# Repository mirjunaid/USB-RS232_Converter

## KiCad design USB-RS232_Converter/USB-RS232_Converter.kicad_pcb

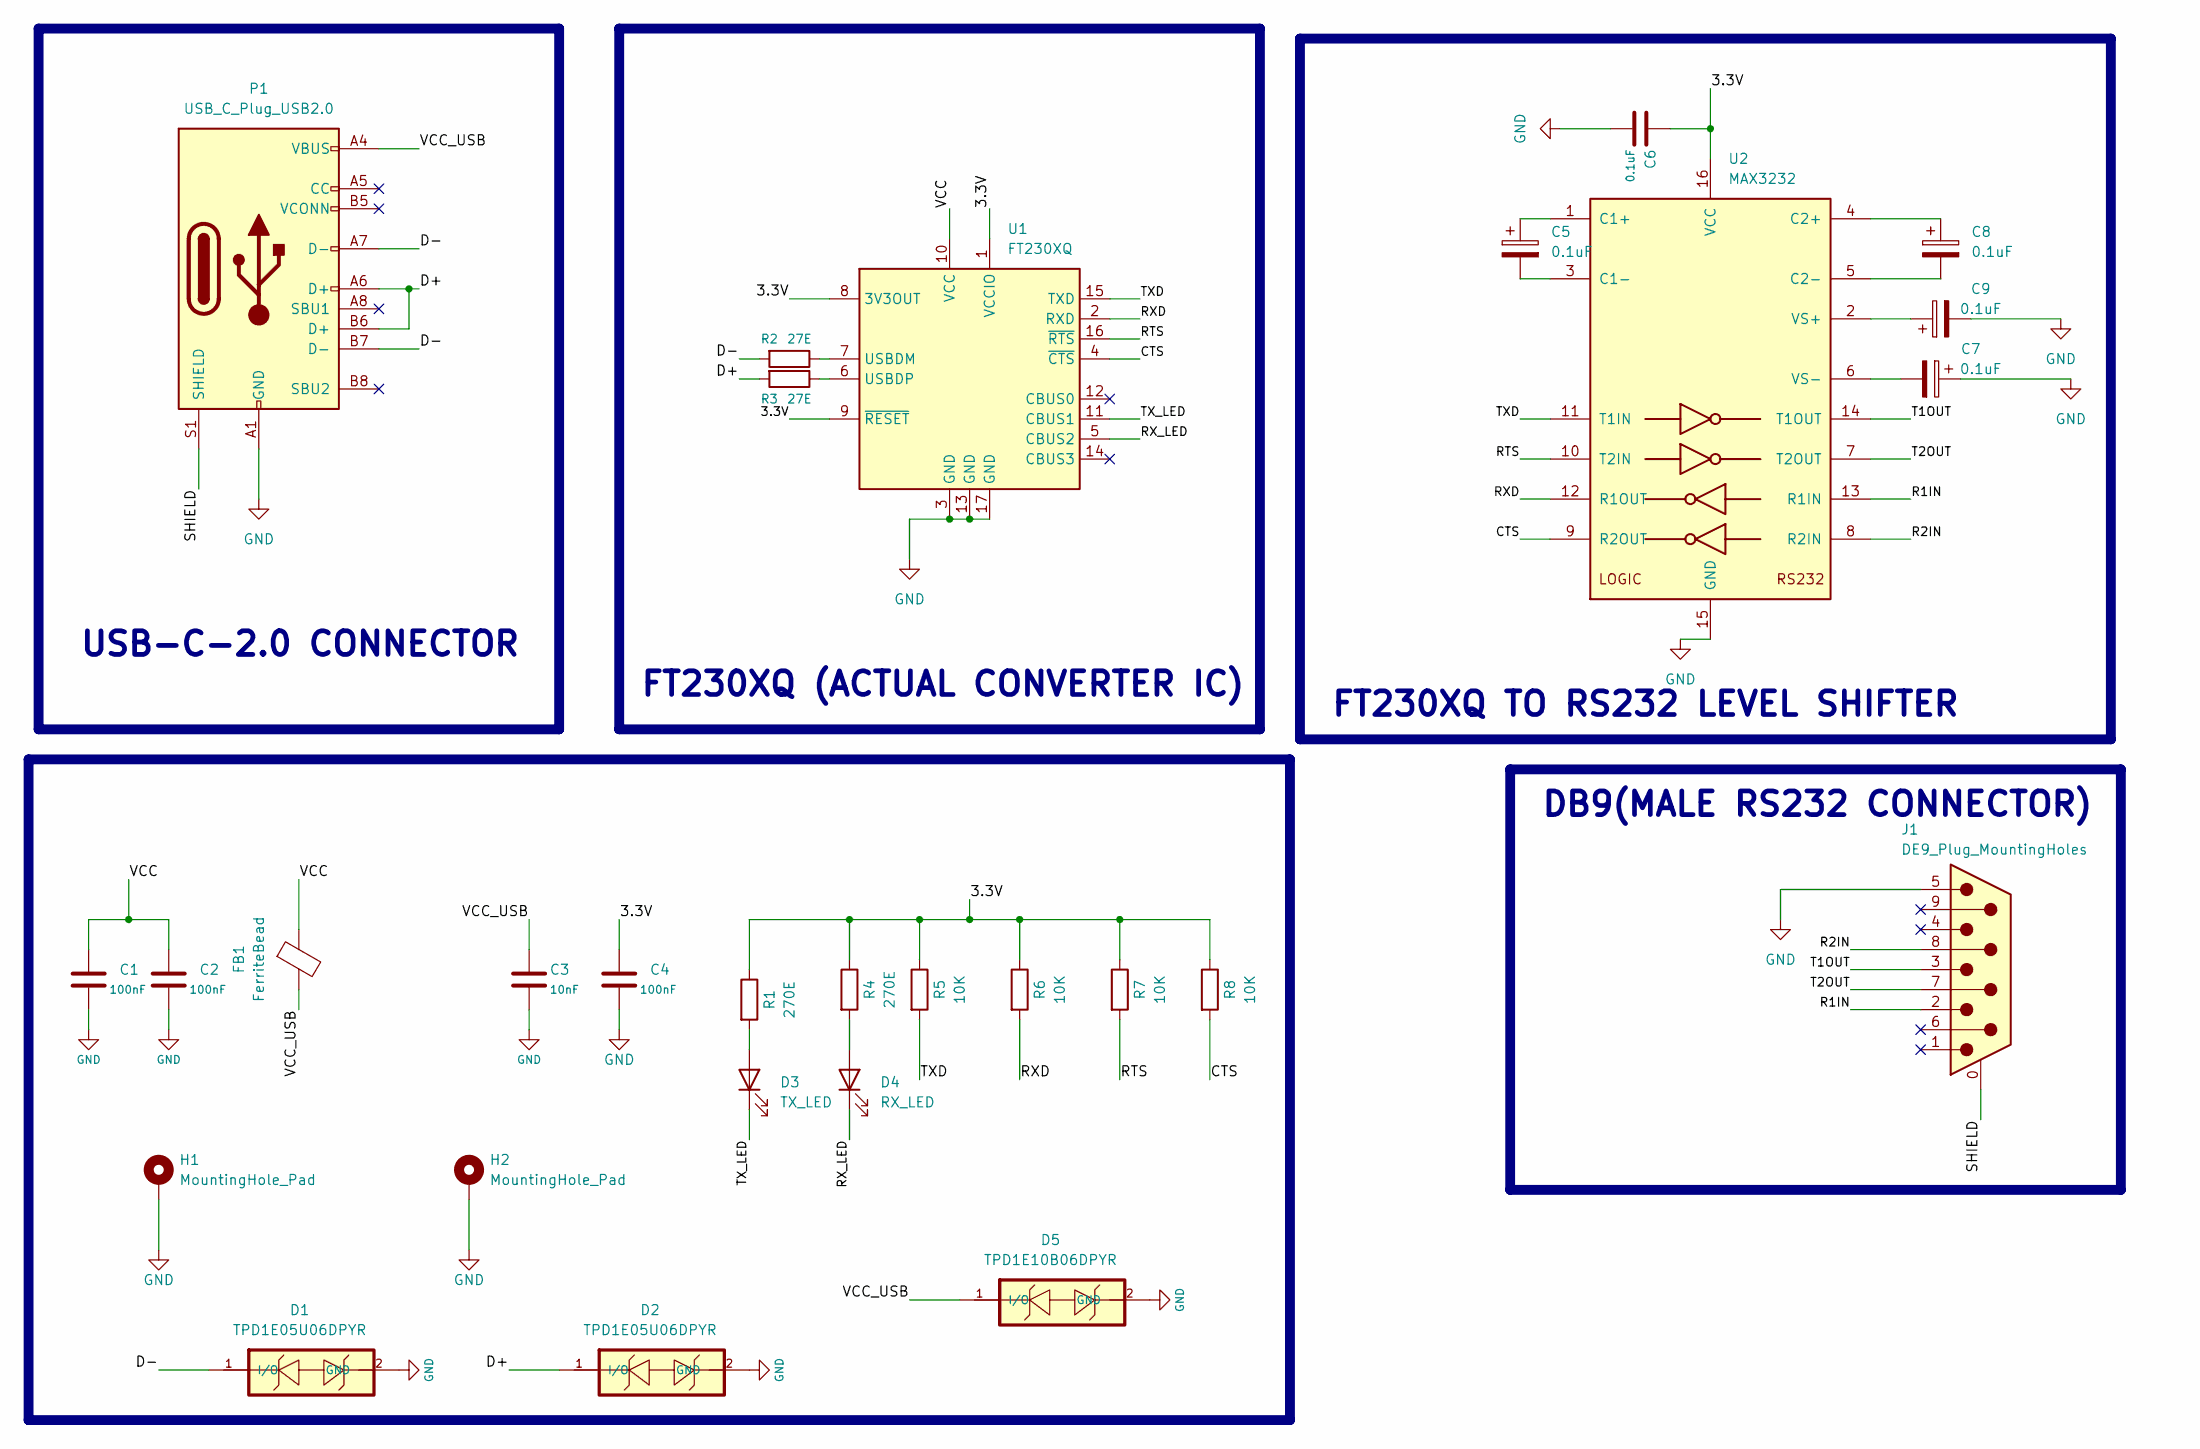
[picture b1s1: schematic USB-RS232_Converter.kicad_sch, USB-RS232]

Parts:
C1, C2, C4: 100nF; C_0201_0603Metric
C3: 10nF; C_0201_0603Metric
C5, C6, C7, C8, C9: 0.1uF; C_0201_0603Metric
D1, D2: TPD1E05U06DPYR; C_0201_0603Metric
D3: TX_LED; LED_1812_4532Metric
D4: RX_LED; LED_1812_4532Metric
D5: TPD1E10B06DPYR; C_0201_0603Metric
FB1: FerriteBead; C_0805_2012Metric
H1, H2: MountingHole_Pad; MountingHole_2.5mm_Pad
J1: DE9_Plug_MountingHoles; DSUB-9_Male_Horizontal_P2.77x2.84mm_EdgePinOffset4.94mm_Hou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
P1: USB_C_Plug_USB2.0; USB_C_Receptacle_HRO_TYPE-C-31-M-12
R1, R4: 270E; R_0603_1608Metric
R2, R3: 27E; R_0603_1608Metric
R5, R6, R7, R8: 10K; R_1206_3216Metric
U1: FT230XQ; QFN-16-1EP_4x4mm_P0.65mm_EP2.1x2.1mm
U2: MAX3232; SOIC-16W_7.5x10.3mm_P1.27mm

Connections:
/3.3V: C4.1, C6.1, R1.1, R4.1, R5.1, R6.1, R7.1, R8.1, U1.1 (VCCIO), U1.8 (3V3OUT), U1.9 (~RESET), U2.16 (VCC)
/CTS: R8.2, U1.4 (~CTS), U2.9 (R2OUT)
/D+: D2.1 (I/O), P1.A6 (D+), P1.B6 (D+), R3.2
/D-: D1.1 (I/O), P1.A7 (D-), P1.B7 (D-), R2.2
/R1IN: J1.2, U2.13 (R1IN)
/R2IN: J1.8, U2.8 (R2IN)
/RTS: R7.2, U1.16 (~RTS), U2.10 (T2IN)
/RXD: R6.2, U1.2 (RXD), U2.12 (R1OUT)
/RX_LED: D4.1 (K), U1.5 (CBUS2)
/SHIELD: J1.0 (PAD), P1.S1 (SHIELD)
/T1OUT: J1.3, U2.14 (T1OUT)
/T2OUT: J1.7, U2.7 (T2OUT)
/TXD: R5.2, U1.15 (TXD), U2.11 (T1IN)
/TX_LED: D3.1 (K), U1.11 (CBUS1)
/VCC: C1.1, C2.1, FB1.1, U1.10 (VCC)
/VCC_USB: C3.1, D5.1 (I/O), FB1.2, P1.A4 (VBUS), P1.A9 (VBUS), P1.B4 (VBUS), P1.B9 (VBUS)
GND: C1.2, C2.2, C3.2, C4.2, C6.2, C7.1, C9.2, D1.2 (GND), D2.2 (GND), D5.2 (GND), H1.1, H2.1, J1.5, P1.A1 (GND), P1.A12 (GND), P1.B1 (GND), P1.B12 (GND), U1.3 (GND), U1.13 (GND), U1.17 (GND), U2.15 (GND)
unnamed: D3.2 (A), R1.2
unnamed: D4.2 (A), R4.2
unnamed: R2.1, U1.7 (USBDM)
unnamed: R3.1, U1.6 (USBDP)
unnamed: C5.1, U2.1 (C1+)
unnamed: C5.2, U2.3 (C1-)
unnamed: C8.1, U2.4 (C2+)
unnamed: C8.2, U2.5 (C2-)
unnamed: C9.1, U2.2 (VS+)
unnamed: C7.2, U2.6 (VS-)

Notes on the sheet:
USB-C-2.0 CONNECTOR
FT230XQ TO RS232 LEVEL SHIFTER
DB9(MALE RS232 CONNECTOR)
FT230XQ (ACTUAL CONVERTER IC)

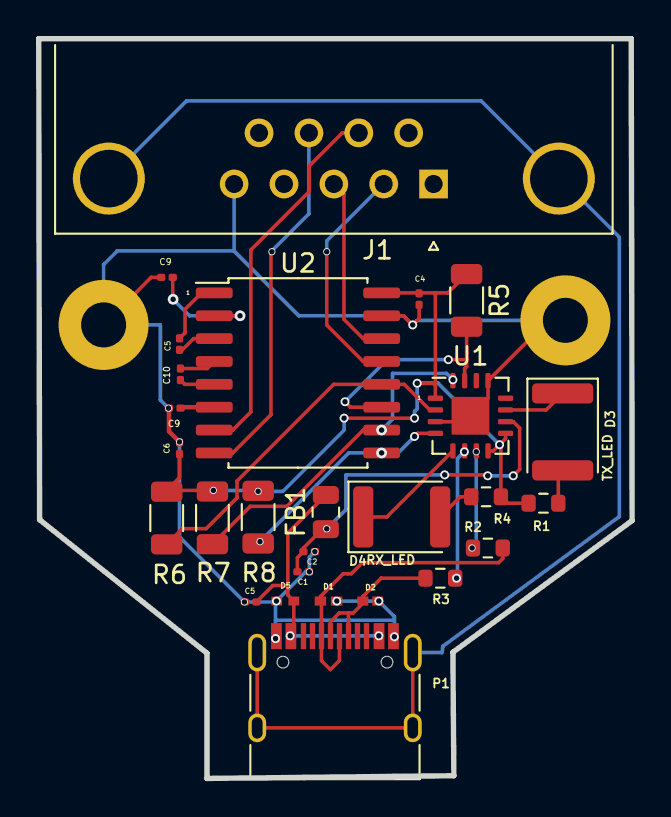
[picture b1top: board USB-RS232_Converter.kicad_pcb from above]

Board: 2 copper layers, 33.0 x 41.1 mm, 29 parts (0 on the bottom side), 27 nets.
